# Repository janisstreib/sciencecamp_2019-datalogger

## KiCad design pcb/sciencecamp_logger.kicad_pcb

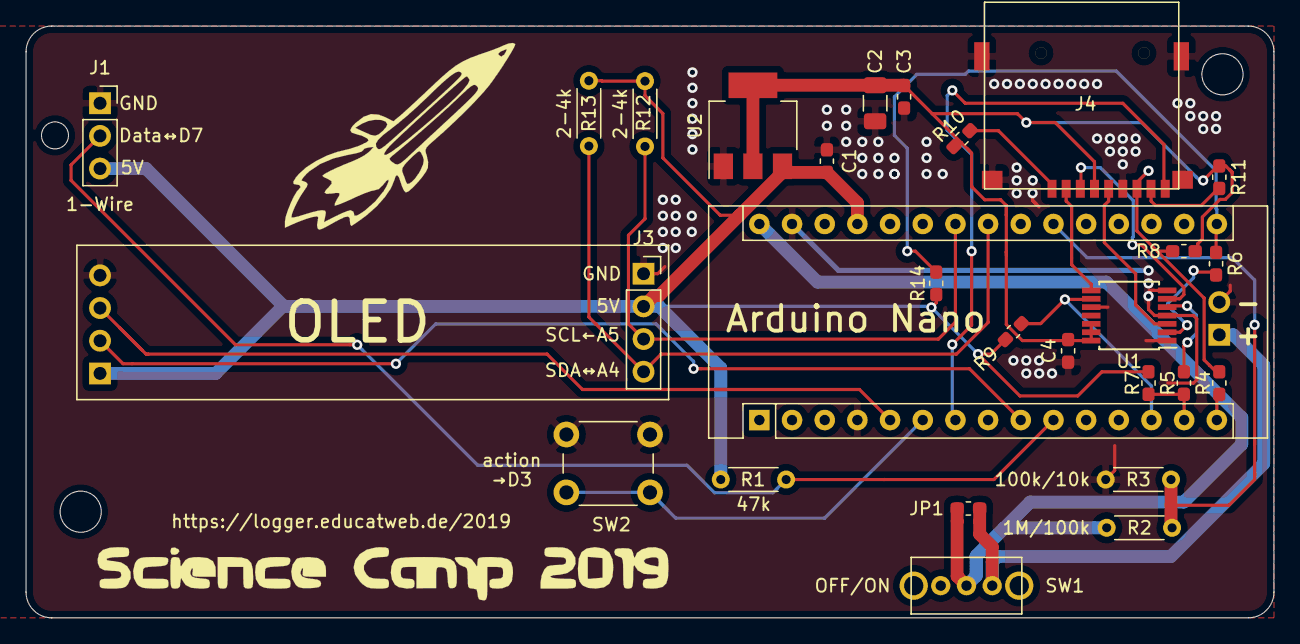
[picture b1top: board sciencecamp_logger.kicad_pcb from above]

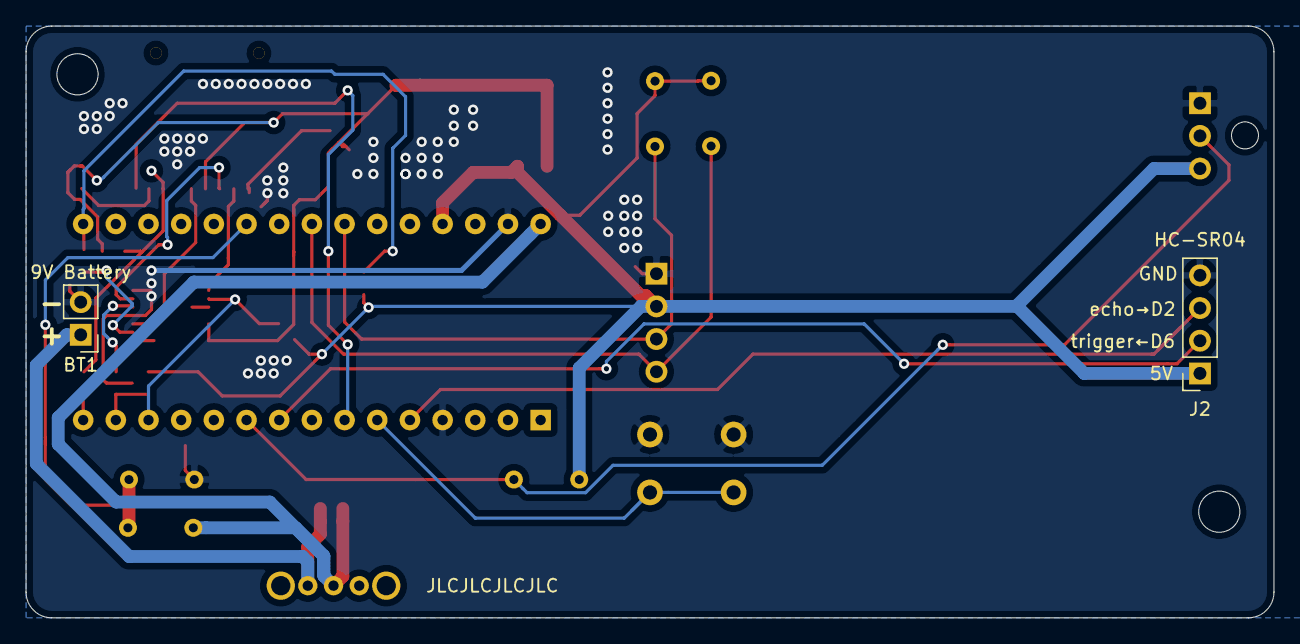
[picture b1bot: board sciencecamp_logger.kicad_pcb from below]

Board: 2 copper layers, 97.0 x 46.0 mm, 29 parts (2 on the bottom side), 25 nets.

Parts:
A1: Arduino Nano; Arduino_Nano
BT1: 9V Battery; PinHeader_1x02_P2.54mm_Vertical
C1, C3: 0.01uF; C_0603_1608Metric_Pad1.05x0.95mm_HandSolder
C2: 10uF; C_1206_3216Metric
C4: 0.1u; C_0603_1608Metric_Pad1.05x0.95mm_HandSolder
J1: 1-Wire; PinSocket_1x03_P2.54mm_Vertical
J2: HC-SR04; PinSocket_1x04_P2.54mm_Vertical
J3: OLED; 12832_SSD1306
J4: Micro_SD_Card_Det; SOFNG_TF-15_15
JP1: switch_bypass; R_0603_1608Metric_Pad1.05x0.95mm_HandSolder
R1: 47k; R_Axial_DIN0204_L3.6mm_D1.6mm_P5.08mm_Horizontal
R2: 1M/100k; R_Axial_DIN0204_L3.6mm_D1.6mm_P5.08mm_Horizontal
R3: 100k/10k; R_Axial_DIN0204_L3.6mm_D1.6mm_P5.08mm_Horizontal
R4, R5, R6: 0; R_0603_1608Metric_Pad1.05x0.95mm_HandSolder
R7: 47/70k; R_0603_1608Metric_Pad1.05x0.95mm_HandSolder
R8, R10, R11: 47/50k; R_0603_1608Metric_Pad1.05x0.95mm_HandSolder
R9, R14: 47k/50k; R_0603_1608Metric_Pad1.05x0.95mm_HandSolder
R12, R13: 2-4k; R_Axial_DIN0204_L3.6mm_D1.6mm_P5.08mm_Horizontal
SW1: OFF/ON; OS102011MA1QN1
SW2: action; SW_PUSH_6mm_H13mm
U1: 74LVC125; TSSOP-14_4.4x5mm_P0.65mm
U2: AMS1117-3.3; SOT-223-3_TabPin2

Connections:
+5V: A1.27, C1.1, J1.3, J2.1, J3.2, R1.1, R7.2, R9.1, R12.1, R13.1, R14.1, U2.3
/ECHO: A1.5, J2.3
/SCL: A1.24, J3.3, R12.2
/SDA: A1.23, J3.4, R13.2
/TRIGGER: A1.9, J2.2
GND: A1.4, A1.29, BT1.2, C1.2, C2.2, C3.2, C4.2, J1.1, J2.4, J3.1, J4.6, J4.11, R3.2, SW2.1, U1.1, U1.4, U1.7, U1.10, U2.1
MISO: A1.15, R4.2
MOSI: A1.14, R5.2, R7.1
unnamed: A1.6, SW2.2
unnamed: A1.10, J1.2, R1.2
unnamed: A1.21, R2.2, R3.1
unnamed: A1.30, JP1.1, R2.1, SW1.2
unnamed: BT1.1, JP1.2, SW1.3
unnamed: J4.1, R10.2
unnamed: J4.2, U1.8
unnamed: J4.3, U1.6
unnamed: J4.5, U1.3
unnamed: J4.7, R4.1, R8.2
unnamed: J4.8, R11.2
unnamed: R5.1, U1.5
unnamed: R6.1, U1.2
SD_3V3: C2.1, C3.1, C4.1, J4.4, R8.1, R10.1, R11.1, U1.12, U1.13, U1.14, U2.2
SD_DETECT: A1.7, J4.10
SD_SS: A1.13, R9.2, U1.9
SPI_SCK: A1.16, R6.2, R14.2

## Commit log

2019-06-08 init: pcb
2019-06-08 UPD: renamed folder
2019-06-09 UPD: More GND-surface for bat minus
2019-06-09 FIX: correct pullup and connected all buffer inputs
2019-06-09 ADD: additional pullups
2019-06-09 FIX: overlapping slikscreen
2019-06-09 ADD: url
2019-06-09 UPD: more THT
2019-06-09 UPD: respositioned text
2019-07-02 FIX: server layout issues
    - wrong pin order for sc-card slot
    - wrong pin order for ultrasonic sensor
    - wrong footprint for 10uF cap
    - missing pads for switch footprint
    - missing level convertion for spi chip select
    - unnecessary level conversion for miso
2019-07-02 Slight fixes
2019-07-03 Small fixes
2019-07-04 FIX: correct label and location
2019-07-09 ADD: strain relief for one-wire sensor
2019-07-10 ADD: basic firmware
2019-07-11 FIX: mixed up ultrasonic pins
2019-07-19 CLN: refill
2019-07-19 ADD: jlcpcb customer id
2019-08-09 FIX: imporved performance for temperatrure readings
2019-08-10 ADD: sd support, page for vin
2019-08-10 ADD: greeter
2019-08-11 FIX: file numbering
2019-08-11 FIX: don't output time in serial output
2019-08-11 FIX: memory optimization, overflow bug, loading screen
